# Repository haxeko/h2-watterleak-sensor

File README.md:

# h2-watterleak-sensor

Cảm biến rò rỉ nước chạy pin, kết nối **Matter over Thread**. Chip là **ESP32-H2**, chạy ở chế độ ICD / Sleepy End Device.
Thiết bị dùng được với Apple Home và Home Assistant thông qua Thread Border Router.

## Tiến độ theo giai đoạn

| # | Giai đoạn | Tài liệu | Trạng thái |
|---|---|---|---|
| 1 | Yêu cầu & ngân sách dòng | [docs/01-yeu-cau-va-ngan-sach-dong.md](docs/01-yeu-cau-va-ngan-sach-dong.md) | ✅ Đã chốt |
| 2 | Sơ đồ khối + gán chân GPIO | [docs/02-so-do-khoi-va-gan-chan.md](docs/02-so-do-khoi-va-gan-chan.md) | ✅ Đã chốt |
| 3 | Sơ đồ nguyên lý (KiCad 9) | [docs/03-so-do-nguyen-ly.md](docs/03-so-do-nguyen-ly.md) · [PDF](hardware/h2-leak-sensor/h2-leak-sensor_schematic.pdf) · [project](hardware/) | ✅ Xong, ERC 0 lỗi |
| 4 | Layout PCB, DRC, BOM, CPL, vỏ in 3D | [docs/04-layout-pcb.md](docs/04-layout-pcb.md) · [Gerber zip](hardware/h2-leak-sensor/fab/h2-leak-sensor_gerbers.zip) · [vỏ](hardware/enclosure/) | ✅ Xong, DRC 0 lỗi / 0 cảnh báo, chờ duyệt |
| 5 | Firmware (ESP-IDF v5.5.5 + esp-matter release/v1.6) | [docs/05-firmware.md](docs/05-firmware.md) · [firmware/](firmware/) | ✅ Đã viết code, chờ bạn build thử |
| 6 | Kế hoạch test (dòng ngủ, thử nước, tầm Thread) | [docs/06-ke-hoach-test.md](docs/06-ke-hoach-test.md) | ✅ Kế hoạch + công cụ xong, chờ board |

## Công cụ

| Script | Giai đoạn | Việc |
|---|---|---|
| `tools/power_budget.py` | 1, 6 | Mô hình dòng và tuổi thọ pin |
| `hardware/tools/gen_*.py`, `route.py`, `fab_outputs.py` | 3–4 | Sinh sơ đồ, board, đi dây, file sản xuất (xem [hardware/README.md](hardware/README.md)) |
| `tools/ppk2_analyze.py` | 6 | Phân tích bản ghi PPK2: dòng sàn/TB, poll, độ trễ báo rò, tuổi thọ |
| `tools/leak_test_runner.py` + `tools/leak_sim/` | 6 | Bộ giả lập nước + đo độ trễ / chống báo giả qua Home Assistant |

- `tools/power_budget.py`: mô hình ngân sách dòng và tuổi thọ pin, chỉ dùng thư viện chuẩn Python 3.

  ```sh
  python3 tools/power_budget.py              # in toàn bộ bảng (dùng trong tài liệu GĐ1)
  python3 tools/power_budget.py --sai 10     # thử slow-poll 10 s
  python3 tools/power_budget.py --floor 31.5 # thay sàn ngủ bằng số đo thật (GĐ6)
  ```

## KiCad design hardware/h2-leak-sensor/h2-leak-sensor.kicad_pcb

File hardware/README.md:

# Phần cứng — h2-watterleak-sensor rev A (KiCad 9)

```
hardware/
├── h2-leak-sensor/                 project KiCad 9 (mở h2-leak-sensor.kicad_pro)
│   ├── h2-leak-sensor.kicad_sch    trang gốc (4 sheet con)
│   ├── power.kicad_sch  mcu.kicad_sch  probe.kicad_sch  ui.kicad_sch
│   ├── h2-leak-sensor_schematic.pdf
│   ├── h2-leak-sensor.kicad_pcb    board 70 x 42 mm, 2 lớp, đã đi dây (luật DRC trong .kicad_pro)
│   ├── fab/                        Gerber zip, BOM + CPL cho JLCPCB, PDF lắp ráp, báo cáo DRC
│   ├── bom/h2-leak-sensor_bom.csv  BOM gộp theo giá trị (không gồm module ESP)
│   ├── lib/h2leak.kicad_sym        symbol riêng: ESP32-H2-WROOM-02C, Electrode_Comb
│   ├── lib/h2leak.pretty/          footprint riêng (module, TPS63900 hàn tay, 4020, điện cực)
│   ├── sym-lib-table  fp-lib-table bảng thư viện của project (thư viện "h2leak")
├── enclosure/                      vỏ in 3D: h2-leak-enclosure.scad + 3 file STL
└── tools/
    ├── sexpr.py                    đọc/ghi S-expression của KiCad (không phụ thuộc gì)
    ├── gen_lib.py                  sinh thư viện riêng
    ├── gen_sch.py                  sinh sơ đồ nguyên lý phân cấp
    ├── gen_pcb.py                  đặt linh kiện, luật DRC, vùng đổ GND, keep-out, silkscreen
    ├── route.py                    router A* 2 lớp + đổ GND + sửa liên thông GND
    └── fab_outputs.py              Gerber, drill, BOM/CPL JLCPCB, PDF lắp ráp, DRC
```

## Tái tạo và kiểm tra

Cần KiCad 9 (`kicad-cli`) và Python 3.

```sh
python3 hardware/tools/gen_lib.py
python3 hardware/tools/gen_sch.py
cd hardware/h2-leak-sensor
kicad-cli sch erc --severity-all h2-leak-sensor.kicad_sch          # kỳ vọng: 0 violations
kicad-cli sch export pdf -o h2-leak-sensor_schematic.pdf h2-leak-sensor.kicad_sch
kicad-cli sch export bom --fields 'Reference,Value,Footprint,LCSC,MPN,Manufacturer,${QUANTITY}' \
    --group-by 'Value,Footprint,LCSC' -o bom/h2-leak-sensor_bom.csv h2-leak-sensor.kicad_sch
```

Layout và file sản xuất (cần thêm `numpy`):

```sh
python3 hardware/tools/gen_pcb.py        # đọc netlist từ sơ đồ, đặt linh kiện
python3 hardware/tools/route.py          # đi dây, đổ GND, kiểm tra liên thông GND (~4 phút)
python3 hardware/tools/fab_outputs.py    # fab/: Gerber zip, BOM, CPL, PDF lắp ráp, DRC json
cd hardware/h2-leak-sensor
kicad-cli pcb drc --severity-all --schematic-parity h2-leak-sensor.kicad_pcb   # kỳ vọng: 0 / 0 / 0
```

> `gen_pcb.py` tạo board mới từ đầu, nên mọi chỉnh tay trên board sẽ mất.
> Nếu đã chỉnh tay thì chỉ chạy `route.py --gnd-only` (kiểm tra và sửa liên thông GND) và `fab_outputs.py`.

Tài liệu thiết kế:
- [docs/02-so-do-khoi-va-gan-chan.md](../docs/02-so-do-khoi-va-gan-chan.md): sơ đồ khối và gán chân.
- [docs/03-so-do-nguyen-ly.md](../docs/03-so-do-nguyen-ly.md): sơ đồ nguyên lý.
- [docs/04-layout-pcb.md](../docs/04-layout-pcb.md): layout, DRC, file sản xuất, vỏ.

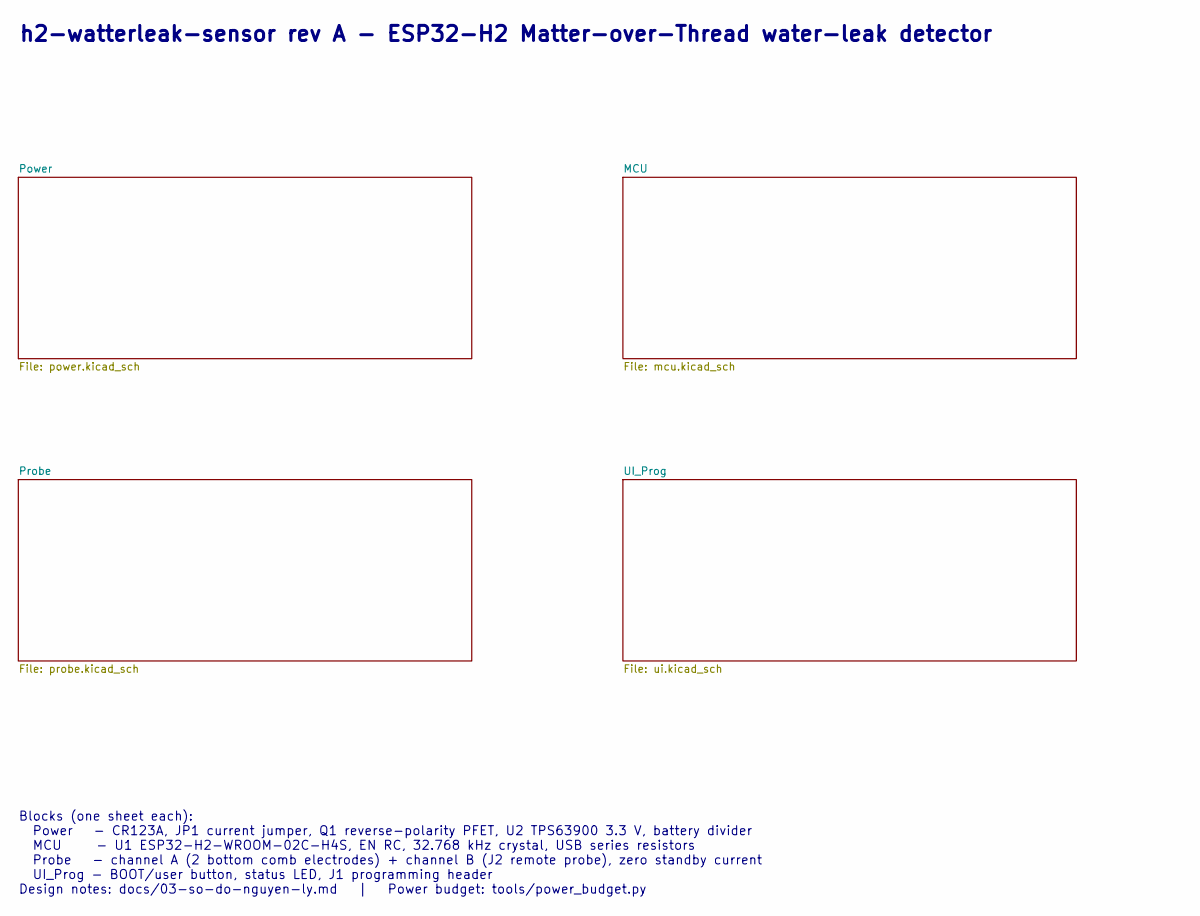
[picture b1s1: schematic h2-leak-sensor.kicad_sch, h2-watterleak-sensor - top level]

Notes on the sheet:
h2-watterleak-sensor rev A - ESP32-H2 Matter-over-Thread water-leak detector
Blocks (one sheet each): Power - CR123A, JP1 current jumper, Q1 reverse-polarity PFET, U2 TPS63900 3.3 V, battery divider MCU - U1 ESP32-H2-WROOM-02C-H4S, EN RC, 32.768 kHz crystal, USB series resistors Probe - channel A (2 bottom comb electrodes) + channel B (J2 remote probe), zero standby current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

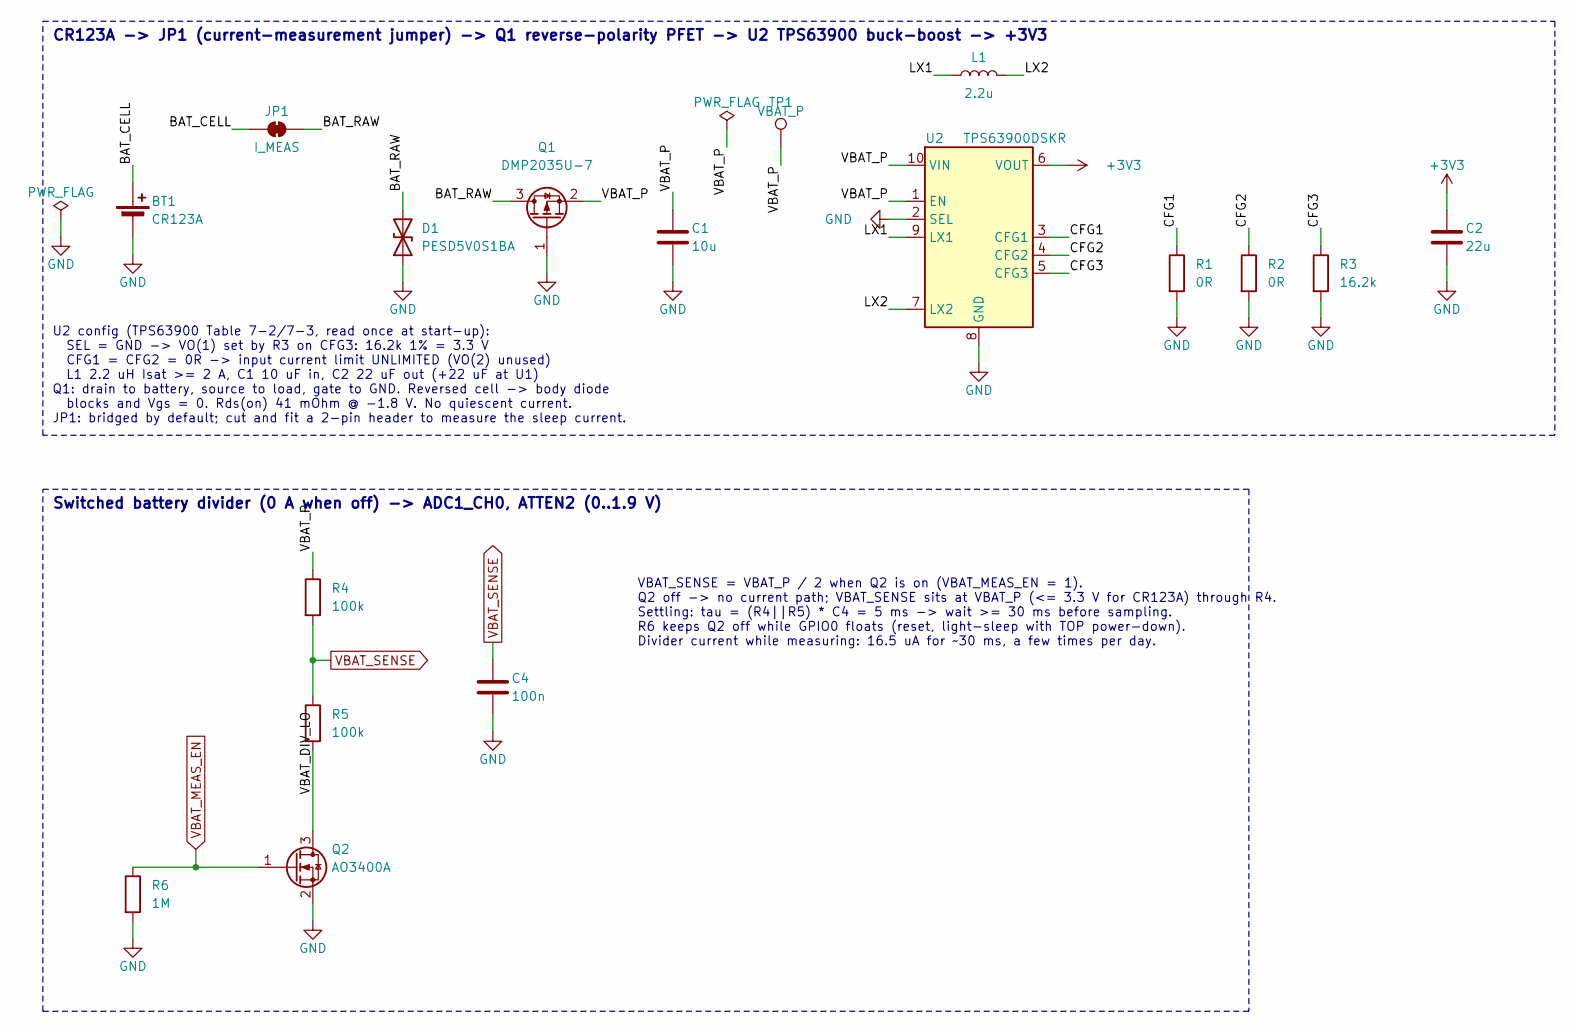
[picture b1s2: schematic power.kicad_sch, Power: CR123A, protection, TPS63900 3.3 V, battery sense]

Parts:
BT1: CR123A; BatteryHolder_Bulgin_BX0123_1xCR123; MPN BX0123 (DigiKey 708-1412-ND)
C1: 10u; C_0603_1608Metric_Pad1.08x0.95mm_HandSolder; MPN CL10A106KP8NNNC; LCSC C19702
C2: 22u; C_0805_2012Metric_Pad1.18x1.45mm_HandSolder; MPN CL21A226MAQNNNE; LCSC C45783
C4: 100n; C_0603_1608Metric_Pad1.08x0.95mm_HandSolder; MPN CC0603KRX7R9BB104; LCSC C14663
D1: PESD5V0S1BA; D_SOD-323_HandSoldering; MPN PESD5V0S1BA,115; LCSC C19224
JP1: I_MEAS; SolderJumper-2_P1.3mm_Bridged_RoundedPad1.0x1.5mm; MPN solder jumper (bridged)
L1: 2.2u; L_Sunlord_WPN4020H_HandSolder; MPN WPN4020H2R2MT; LCSC C98361
Q1: DMP2035U-7; SOT-23_Handsoldering; MPN DMP2035U-7; LCSC C110499
Q2: AO3400A; SOT-23_Handsoldering; MPN AO3400A; LCSC C20917
R1, R2: 0R; R_0603_1608Metric_Pad0.98x0.95mm_HandSolder; MPN 0603WAF0000T5E; LCSC C21189
R3: 16.2k; R_0603_1608Metric_Pad0.98x0.95mm_HandSolder; MPN 0603WAF1622T5E; LCSC C22885
R4, R5: 100k; R_0603_1608Metric_Pad0.98x0.95mm_HandSolder; MPN 0603WAF1003T5E; LCSC C25803
R6: 1M; R_0603_1608Metric_Pad0.98x0.95mm_HandSolder; MPN 0603WAF1004T5E; LCSC C22935
TP1: VBAT_P; TestPoint_Pad_D1.5mm; MPN test pad
U2: TPS63900DSKR; TPS63900_WSON-10_2.5x2.5mm_HandSolder; MPN TPS63900DSKR; LCSC C1518762

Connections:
+3V3: C2.1, U2.6 (VOUT); also elsewhere on the board
/Power/BAT_CELL: BT1.1 (+), JP1.1 (A)
/Power/BAT_RAW: D1.2 (A2), JP1.2 (B), Q1.3 (D)
/Power/CFG1: R1.1, U2.3 (CFG1)
/Power/CFG2: R2.1, U2.4 (CFG2)
/Power/CFG3: R3.1, U2.5 (CFG3)
/Power/LX1: L1.1, U2.9 (LX1)
/Power/LX2: L1.2, U2.7 (LX2)
/Power/VBAT_DIV_LO: Q2.3 (D), R5.2
/Power/VBAT_P: C1.1, Q1.2 (S), R4.1, TP1.1, U2.1 (EN), U2.10 (VIN)
GND: BT1.2 (-), C1.2, C2.2, C4.2, D1.1 (A1), Q1.1 (G), Q2.2 (S), R1.2, R2.2, R3.2, R6.2, U2.2 (SEL), U2.8 (GND), U2.11 (GND); also elsewhere on the board
VBAT_MEAS_EN: Q2.1 (G), R6.1; also elsewhere on the board
VBAT_SENSE: C4.1, R4.2, R5.1; also elsewhere on the board

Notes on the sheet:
CR123A -> JP1 (current-measurement jumper) -> Q1 reverse-polarity PFET -> U2 TPS63900 buck-boost -> +3V3
U2 config (TPS63900 Table 7-2/7-3, read once at start-up): SEL = GND -> VO(1) set by R3 on CFG3: 16.2k 1% = 3.3 V CFG1 = CFG2 = 0R -> input current limit UNLIMITED (VO(2) unused) L1 2.2 uH Isat >= 2 A, C1 10 uF in, C2 22 uF out (+22 uF at U1) Q1: drain to battery, source to load, gate to GND. Rever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
Switched battery divider (0 A when off) -> ADC1_CH0, ATTEN2 (0..1.9 V)
VBAT_SENSE = VBAT_P / 2 when Q2 is on (VBAT_MEAS_EN = 1). Q2 off -> no current path; VBAT_SENSE sits at VBAT_P (<= 3.3 V for CR123A) through R4. Settling: tau = (R4||R5) * C4 = 5 ms -> wait >= 30 ms before sampling. R6 keeps Q2 off while GPIO0 floats (reset, light-sleep with TOP power-down). Divide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

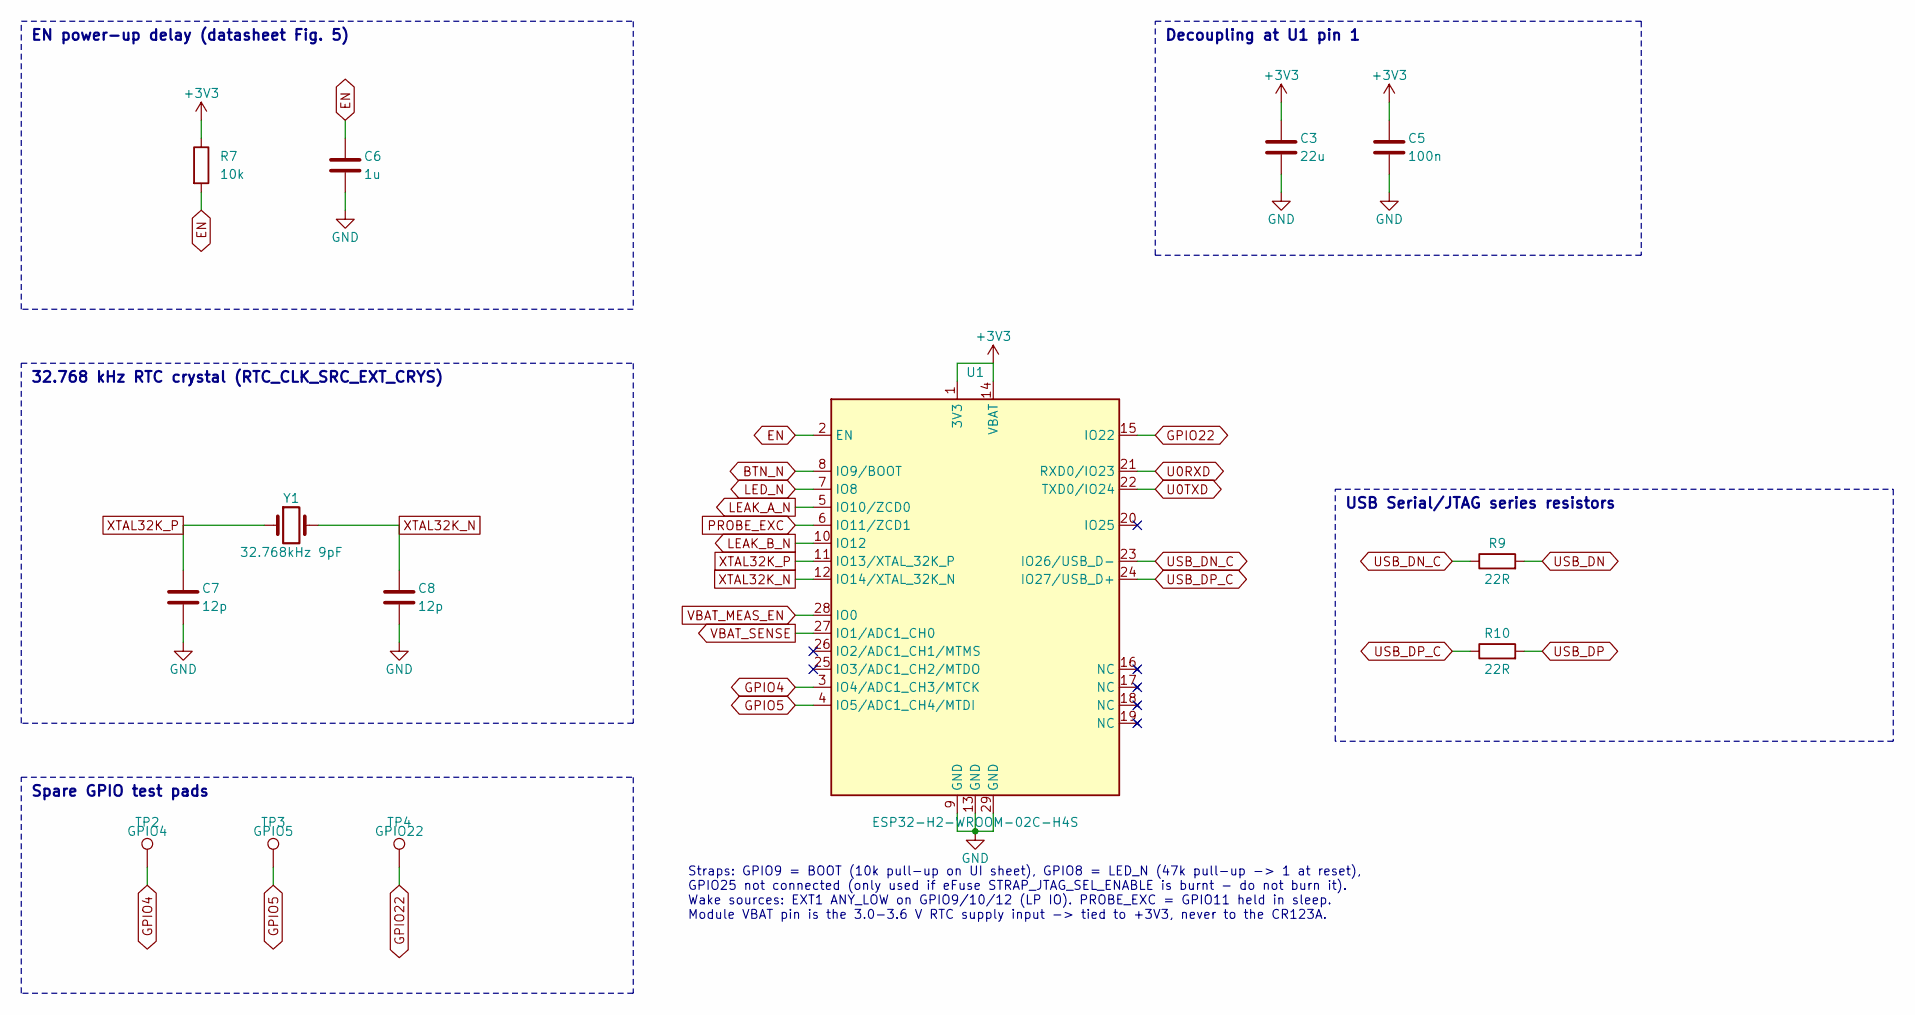
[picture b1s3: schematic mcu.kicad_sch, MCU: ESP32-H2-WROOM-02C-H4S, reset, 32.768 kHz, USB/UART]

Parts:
C3: 22u; C_0805_2012Metric_Pad1.18x1.45mm_HandSolder; MPN CL21A226MAQNNNE; LCSC C45783
C5: 100n; C_0603_1608Metric_Pad1.08x0.95mm_HandSolder; MPN CC0603KRX7R9BB104; LCSC C14663
C6: 1u; C_0603_1608Metric_Pad1.08x0.95mm_HandSolder; MPN CL10A105KB8NNNC; LCSC C15849
C7, C8: 12p; C_0603_1608Metric_Pad1.08x0.95mm_HandSolder; MPN CL10C120JB8NNNC; LCSC C38523
R7: 10k; R_0603_1608Metric_Pad0.98x0.95mm_HandSolder; MPN 0603WAF1002T5E; LCSC C25804
R9, R10: 22R; R_0603_1608Metric_Pad0.98x0.95mm_HandSolder; MPN 0603WAF220JT5E; LCSC C23345
TP2: GPIO4; TestPoint_Pad_D1.5mm; MPN test pad
TP3: GPIO5; TestPoint_Pad_D1.5mm; MPN test pad
TP4: GPIO22; TestPoint_Pad_D1.5mm; MPN test pad
U1: ESP32-H2-WROOM-02C-H4S; ESP32-H2-WROOM-02C; MPN ESP32-H2-WROOM-02C-H4S
Y1: 32.768kHz 9pF; Crystal_SMD_3215-2Pin_3.2x1.5mm; MPN Q13FC13500003; LCSC C99010

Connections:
+3V3: C3.1, C5.1, R7.1, U1.1 (3V3), U1.14 (VBAT); also elsewhere on the board
BTN_N: U1.8 (IO9/BOOT); also elsewhere on the board
EN: C6.1, R7.2, U1.2 (EN); also elsewhere on the board
GND: C3.2, C5.2, C6.2, C7.2, C8.2, U1.9 (GND), U1.13 (GND), U1.29 (GND); also elsewhere on the board
GPIO4: TP2.1, U1.3 (IO4/ADC1_CH3/MTCK)
GPIO5: TP3.1, U1.4 (IO5/ADC1_CH4/MTDI)
GPIO22: TP4.1, U1.15 (IO22)
LEAK_A_N: U1.5 (IO10/ZCD0); also elsewhere on the board
LEAK_B_N: U1.10 (IO12); also elsewhere on the board
LED_N: U1.7 (IO8); also elsewhere on the board
PROBE_EXC: U1.6 (IO11/ZCD1); also elsewhere on the board
U0RXD: U1.21 (RXD0/IO23); also elsewhere on the board
U0TXD: U1.22 (TXD0/IO24); also elsewhere on the board
USB_DN: R9.2; also elsewhere on the board
USB_DN_C: R9.1, U1.23 (IO26/USB_D-)
USB_DP: R10.2; also elsewhere on the board
USB_DP_C: R10.1, U1.24 (IO27/USB_D+)
VBAT_MEAS_EN: U1.28 (IO0); also elsewhere on the board
VBAT_SENSE: U1.27 (IO1/ADC1_CH0); also elsewhere on the board
XTAL32K_N: C8.1, U1.12 (IO14/XTAL_32K_N), Y1.2
XTAL32K_P: C7.1, U1.11 (IO13/XTAL_32K_P), Y1.1

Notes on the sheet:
Decoupling at U1 pin 1
EN power-up delay (datasheet Fig. 5)
32.768 kHz RTC crystal (RTC_CLK_SRC_EXT_CRYS)
USB Serial/JTAG series resistors
Spare GPIO test pads
Straps: GPIO9 = BOOT (10k pull-up on UI sheet), GPIO8 = LED_N (47k pull-up -> 1 at reset), GPIO25 not connected (only used if eFuse STRAP_JTAG_SEL_ENABLE is burnt - do not burn it). Wake sources: EXT1 ANY_LOW on GPIO9/10/12 (LP IO). PROBE_EXC = GPIO11 held in sleep. Module VBAT pin is the 3.0-3.6 V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

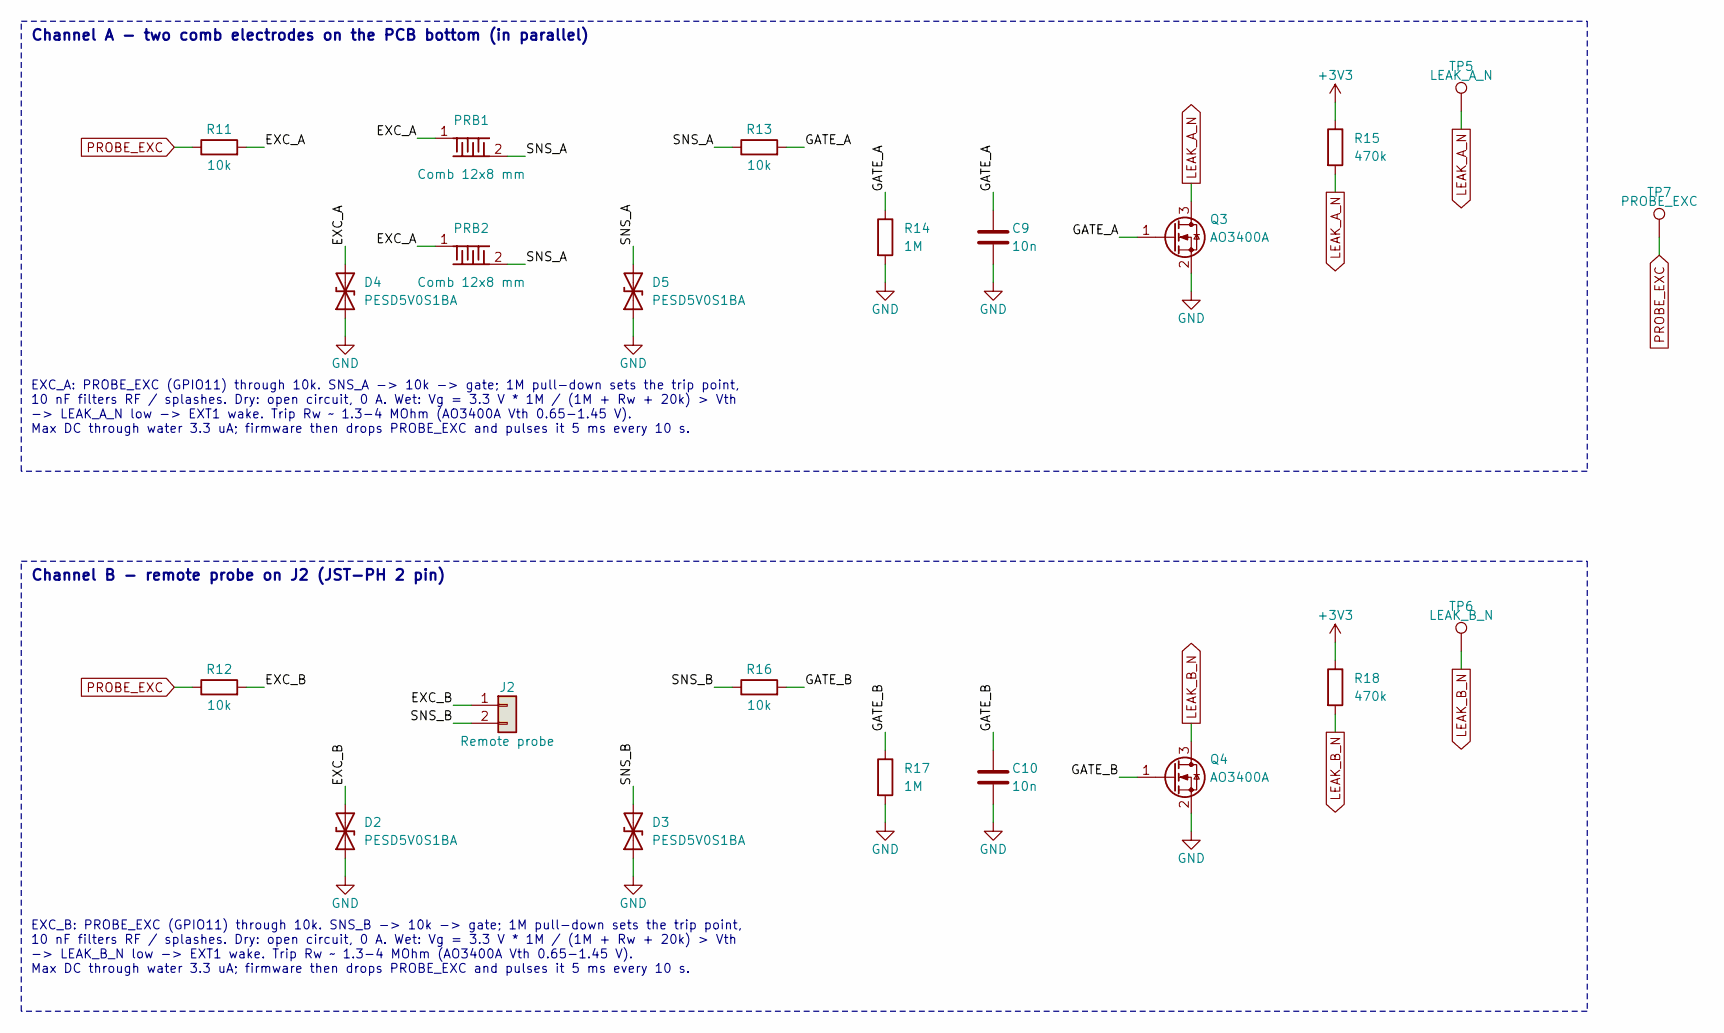
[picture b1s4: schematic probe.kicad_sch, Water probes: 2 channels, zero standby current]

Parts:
C9, C10: 10n; C_0603_1608Metric_Pad1.08x0.95mm_HandSolder; MPN 0603B103K500NT; LCSC C57112
D2, D3, D4, D5: PESD5V0S1BA; D_SOD-323_HandSoldering; MPN PESD5V0S1BA,115; LCSC C19224
J2: Remote probe; JST_PH_S2B-PH-K_1x02_P2.00mm_Horizontal; MPN S2B-PH-K-S(LF)(SN); LCSC C173752
PRB1, PRB2: Comb 12x8 mm; Electrode_Comb_12x8mm; MPN PCB copper (ENIG)
Q3, Q4: AO3400A; SOT-23_Handsoldering; MPN AO3400A; LCSC C20917
R11, R12, R13, R16: 10k; R_0603_1608Metric_Pad0.98x0.95mm_HandSolder; MPN 0603WAF1002T5E; LCSC C25804
R14, R17: 1M; R_0603_1608Metric_Pad0.98x0.95mm_HandSolder; MPN 0603WAF1004T5E; LCSC C22935
R15, R18: 470k; R_0603_1608Metric_Pad0.98x0.95mm_HandSolder; MPN 0603WAF4703T5E; LCSC C23178
TP5: LEAK_A_N; TestPoint_Pad_D1.5mm; MPN test pad
TP6: LEAK_B_N; TestPoint_Pad_D1.5mm; MPN test pad
TP7: PROBE_EXC; TestPoint_Pad_D1.5mm; MPN test pad

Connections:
+3V3: R15.1, R18.1; also elsewhere on the board
/Probe/EXC_A: D4.2 (A2), PRB1.1 (EXC), PRB2.1 (EXC), R11.2
/Probe/EXC_B: D2.2 (A2), J2.1, R12.2
/Probe/GATE_A: C9.1, Q3.1 (G), R13.2, R14.1
/Probe/GATE_B: C10.1, Q4.1 (G), R16.2, R17.1
/Probe/SNS_A: D5.2 (A2), PRB1.2 (SNS), PRB2.2 (SNS), R13.1
/Probe/SNS_B: D3.2 (A2), J2.2, R16.1
GND: C9.2, C10.2, D2.1 (A1), D3.1 (A1), D4.1 (A1), D5.1 (A1), Q3.2 (S), Q4.2 (S), R14.2, R17.2; also elsewhere on the board
LEAK_A_N: Q3.3 (D), R15.2, TP5.1; also elsewhere on the board
LEAK_B_N: Q4.3 (D), R18.2, TP6.1; also elsewhere on the board
PROBE_EXC: R11.1, R12.1, TP7.1; also elsewhere on the board

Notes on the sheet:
Channel A - two comb electrodes on the PCB bottom (in parallel)
EXC_A: PROBE_EXC (GPIO11) through 10k. SNS_A -> 10k -> gate; 1M pull-down sets the trip point, 10 nF filters RF / splashes. Dry: open circuit, 0 A. Wet: Vg = 3.3 V * 1M / (1M + Rw + 20k) > Vth -> LEAK_A_N low -> EXT1 wake. Trip Rw ~ 1.3-4 MOhm (AO3400A Vth 0.65-1.45 V). Max DC through water 3.3 uA;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
Channel B - remote probe on J2 (JST-PH 2 pin)
EXC_B: PROBE_EXC (GPIO11) through 10k. SNS_B -> 10k -> gate; 1M pull-down sets the trip point, 10 nF filters RF / splashes. Dry: open circuit, 0 A. Wet: Vg = 3.3 V * 1M / (1M + Rw + 20k) > Vth -> LEAK_B_N low -> EXT1 wake. Trip Rw ~ 1.3-4 MOhm (AO3400A Vth 0.65-1.45 V). Max DC through water 3.3 uA;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

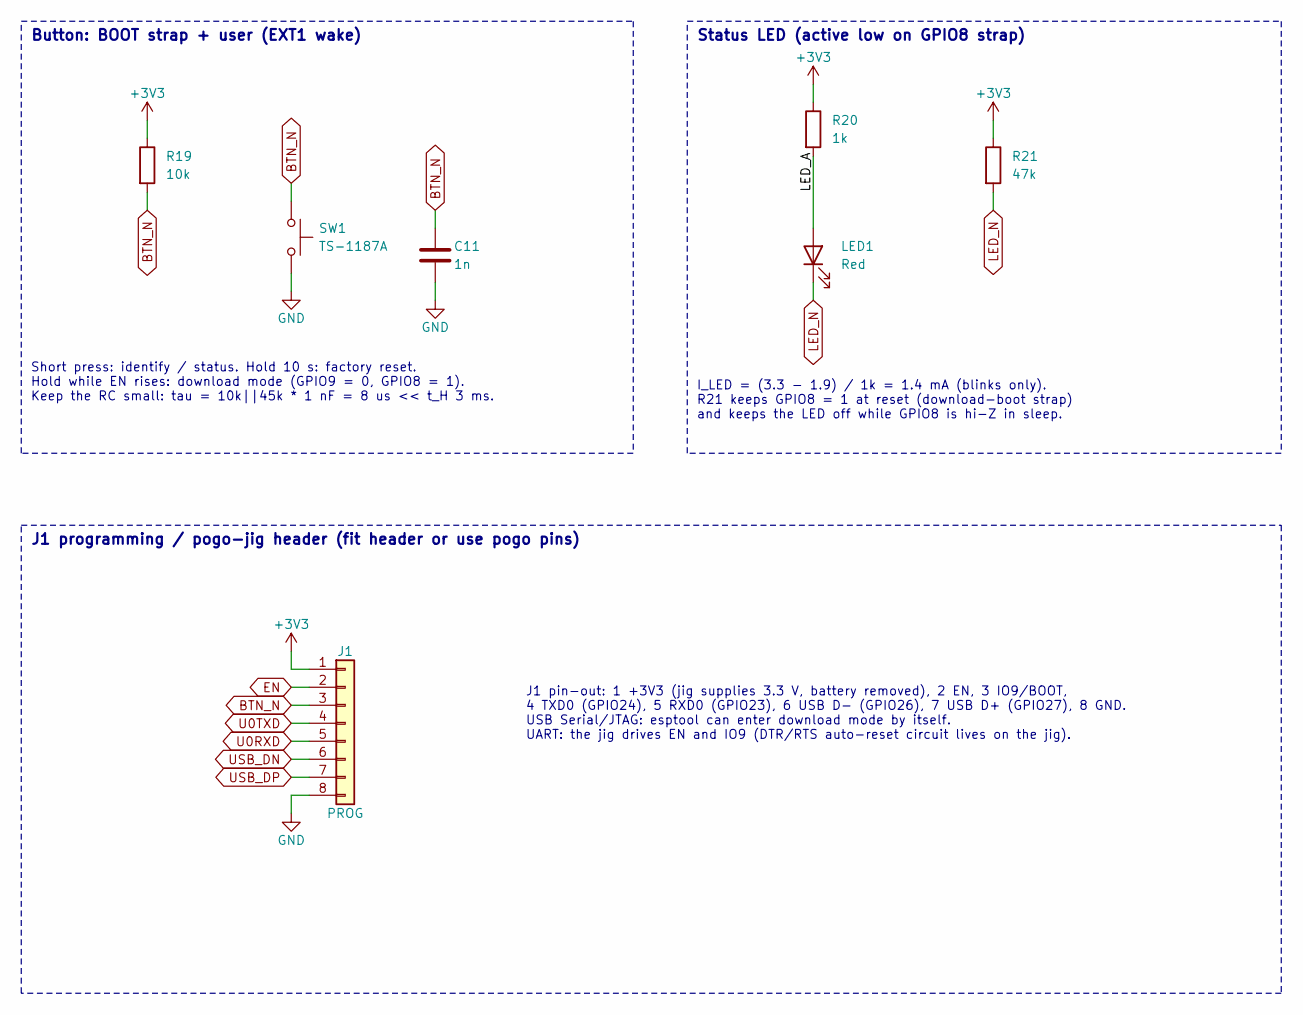
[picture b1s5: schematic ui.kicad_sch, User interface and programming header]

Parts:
C11: 1n; C_0603_1608Metric_Pad1.08x0.95mm_HandSolder; MPN CL10B102KB8NNNC; LCSC C1588
J1: PROG; PinHeader_1x08_P2.54mm_Vertical; MPN 2.54 mm 1x08 header / pogo pads
LED1: Red; LED_0603_1608Metric_Pad1.05x0.95mm_HandSolder; MPN KT-0603R; LCSC C2286
R19: 10k; R_0603_1608Metric_Pad0.98x0.95mm_HandSolder; MPN 0603WAF1002T5E; LCSC C25804
R20: 1k; R_0603_1608Metric_Pad0.98x0.95mm_HandSolder; MPN 0603WAF1001T5E; LCSC C21190
R21: 47k; R_0603_1608Metric_Pad0.98x0.95mm_HandSolder; MPN 0603WAF4702T5E; LCSC C25819
SW1: TS-1187A; SW_Push_1P1T_XKB_TS-1187A; MPN TS-1187A-B-A-B; LCSC C318884

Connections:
+3V3: J1.1, R19.1, R20.1, R21.1; also elsewhere on the board
/UI_Prog/LED_A: LED1.2 (A), R20.2
BTN_N: C11.1, J1.3, R19.2, SW1.1; also elsewhere on the board
EN: J1.2; also elsewhere on the board
GND: C11.2, J1.8, SW1.2; also elsewhere on the board
LED_N: LED1.1 (K), R21.2; also elsewhere on the board
U0RXD: J1.5; also elsewhere on the board
U0TXD: J1.4; also elsewhere on the board
USB_DN: J1.6; also elsewhere on the board
USB_DP: J1.7; also elsewhere on the board

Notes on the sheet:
Button: BOOT strap + user (EXT1 wake)
Short press: identify / status. Hold 10 s: factory reset. Hold while EN rises: download mode (GPIO9 = 0, GPIO8 = 1). Keep the RC small: tau = 10k||45k * 1 nF = 8 us << t_H 3 ms.
Status LED (active low on GPIO8 strap)
I_LED = (3.3 - 1.9) / 1k = 1.4 mA (blinks only). R21 keeps GPIO8 = 1 at reset (download-boot strap) and keeps the LED off while GPIO8 is hi-Z in sleep.
J1 programming / pogo-jig header (fit header or use pogo pins)
J1 pin-out: 1 +3V3 (jig supplies 3.3 V, battery removed), 2 EN, 3 IO9/BOOT, 4 TXD0 (GPIO24), 5 RXD0 (GPIO23), 6 USB D- (GPIO26), 7 USB D+ (GPIO27), 8 GND. USB Serial/JTAG: esptool can enter download mode by itself. UART: the jig drives EN and IO9 (DTR/RTS auto-reset circuit lives on the jig).

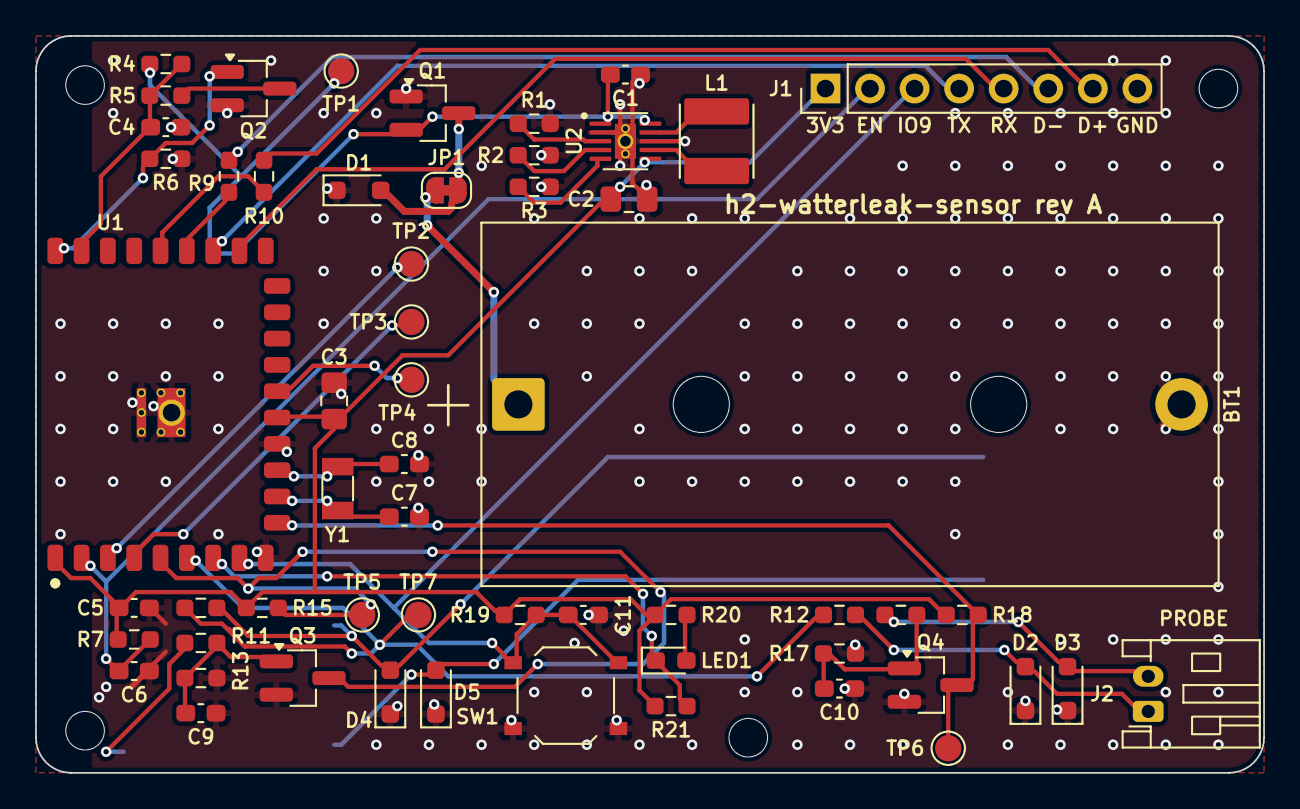
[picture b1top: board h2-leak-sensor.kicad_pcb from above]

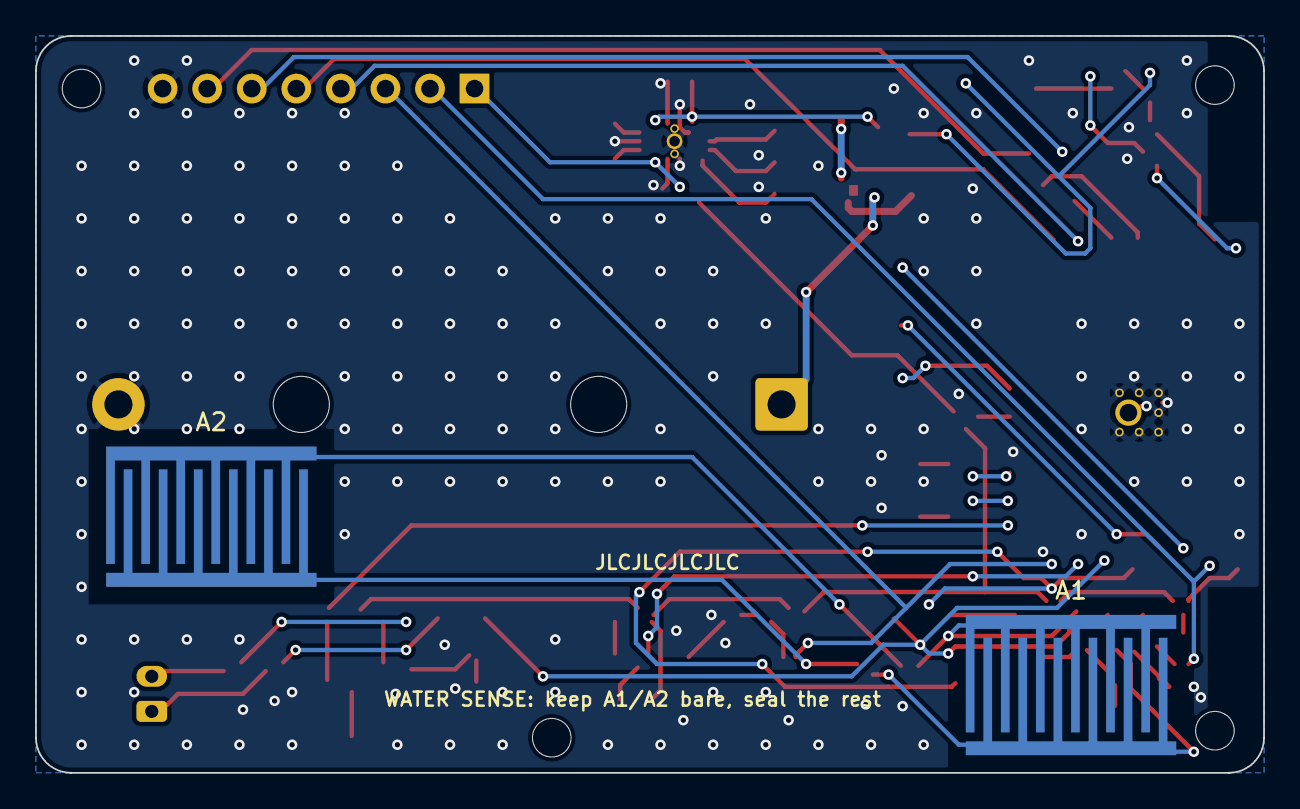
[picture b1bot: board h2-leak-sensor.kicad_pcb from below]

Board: 2 copper layers, 70.0 x 42.0 mm, 63 parts (2 on the bottom side), 37 nets.

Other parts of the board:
H1, H2, H3, H4: MountingHole_M2; MountingHole_2.2mm_M2

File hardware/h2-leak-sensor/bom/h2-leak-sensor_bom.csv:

"Refs","Value","Footprint","LCSC","MPN","Manufacturer","Qty"
"BT1","CR123A","Battery:BatteryHolder_Bulgin_BX0123_1xCR123","","BX0123 (DigiKey 708-1412-ND)","Bulgin","1"
"C1","10u","Capacitor_SMD:C_0603_1608Metric_Pad1.08x0.95mm_HandSolder","C19702","CL10A106KP8NNNC","Samsung","1"
"C2,C3","22u","Capacitor_SMD:C_0805_2012Metric_Pad1.18x1.45mm_HandSolder","C45783","CL21A226MAQNNNE","Samsung","2"
"C4,C5","100n","Capacitor_SMD:C_0603_1608Metric_Pad1.08x0.95mm_HandSolder","C14663","CC0603KRX7R9BB104","YAGEO","2"
"C6","1u","Capacitor_SMD:C_0603_1608Metric_Pad1.08x0.95mm_HandSolder","C15849","CL10A105KB8NNNC","Samsung","1"
"C7,C8","12p","Capacitor_SMD:C_0603_1608Metric_Pad1.08x0.95mm_HandSolder","C38523","CL10C120JB8NNNC","Samsung","2"
"C9,C10","10n","Capacitor_SMD:C_0603_1608Metric_Pad1.08x0.95mm_HandSolder","C57112","0603B103K500NT","FH","2"
"C11","1n","Capacitor_SMD:C_0603_1608Metric_Pad1.08x0.95mm_HandSolder","C1588","CL10B102KB8NNNC","Samsung","1"
"D1-D5","PESD5V0S1BA","Diode_SMD:D_SOD-323_HandSoldering","C19224","PESD5V0S1BA,115","Nexperia","5"
"J1","PROG","Connector_PinHeader_2.54mm:PinHeader_1x08_P2.54mm_Vertical","","2.54 mm 1x08 header / pogo pads","-","1"
"J2","Remote probe","Connector_JST:JST_PH_S2B-PH-K_1x02_P2.00mm_Horizontal","C173752","S2B-PH-K-S(LF)(SN)","JST","1"
"L1","2.2u","h2leak:L_Sunlord_WPN4020H_HandSolder","C98361","WPN4020H2R2MT","Sunlord","1"
"LED1","Red","LED_SMD:LED_0603_1608Metric_Pad1.05x0.95mm_HandSolder","C2286","KT-0603R","Hubei KENTO","1"
"Q1","DMP2035U-7","Package_TO_SOT_SMD:SOT-23_Handsoldering","C110499","DMP2035U-7","Diodes Inc","1"
"Q2-Q4","AO3400A","Package_TO_SOT_SMD:SOT-23_Handsoldering","C20917","AO3400A","AOS","3"
"R1,R2","0R","Resistor_SMD:R_0603_1608Metric_Pad0.98x0.95mm_HandSolder","C21189","0603WAF0000T5E","UNI-ROYAL","2"
"R3","16.2k","Resistor_SMD:R_0603_1608Metric_Pad0.98x0.95mm_HandSolder","C22885","0603WAF1622T5E","UNI-ROYAL","1"
"R4,R5","100k","Resistor_SMD:R_0603_1608Metric_Pad0.98x0.95mm_HandSolder","C25803","0603WAF1003T5E","UNI-ROYAL","2"
"R6,R14,R17","1M","Resistor_SMD:R_0603_1608Metric_Pad0.98x0.95mm_HandSolder","C22935","0603WAF1004T5E","UNI-ROYAL","3"
"R7,R11-R13,R16,R19","10k","Resistor_SMD:R_0603_1608Metric_Pad0.98x0.95mm_HandSolder","C25804","0603WAF1002T5E","UNI-ROYAL","6"
"R9,R10","22R","Resistor_SMD:R_0603_1608Metric_Pad0.98x0.95mm_HandSolder","C23345","0603WAF220JT5E","UNI-ROYAL","2"
"R15,R18","470k","Resistor_SMD:R_0603_1608Metric_Pad0.98x0.95mm_HandSolder","C23178","0603WAF4703T5E","UNI-ROYAL","2"
"R20","1k","Resistor_SMD:R_0603_1608Metric_Pad0.98x0.95mm_HandSolder","C21190","0603WAF1001T5E","UNI-ROYAL","1"
"R21","47k","Resistor_SMD:R_0603_1608Metric_Pad0.98x0.95mm_HandSolder","C25819","0603WAF4702T5E","UNI-ROYAL","1"
"SW1","TS-1187A","Button_Switch_SMD:SW_Push_1P1T_XKB_TS-1187A","C318884","TS-1187A-B-A-B","XKB","1"
"U2","TPS63900DSKR","h2leak:TPS63900_WSON-10_2.5x2.5mm_HandSolder","C1518762","TPS63900DSKR","Texas Instruments","1"
"Y1","32.768kHz 9pF","Crystal:Crystal_SMD_3215-2Pin_3.2x1.5mm","C99010","Q13FC13500003","Seiko Epson","1"

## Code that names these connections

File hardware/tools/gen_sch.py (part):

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    "VBAT_SENSE": "output", "VBAT_MEAS_EN": "input",
    "U0TXD": "bidirectional", "U0RXD": "bidirectional", "USB_DN": "bidirectional", "USB_DP": "bidirectional",
    "XTAL32K_P": "passive", "XTAL32K_N": "passive", "USB_DN_C": "bidirectional", "USB_DP_C": "bidirectional",
    "GPIO4": "bidirectional", "GPIO5": "bidirectional", "GPIO22": "bidirectional",
}


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    sh.connect(u1, {
        "2": "EN", "8": "BTN_N", "7": "LED_N", "5": "LEAK_A_N", "6": "PROBE_EXC", "10": "LEAK_B_N",
        "11": "XTAL32K_P", "12": "XTAL32K_N", "28": "VBAT_MEAS_EN", "27": "VBAT_SENSE",
        "26": None, "25": None, "3": "GPIO4", "4": "GPIO5",
        "15": "GPIO22", "21": "U0RXD", "22": "U0TXD", "20": None, "23": "USB_DN_C", "24": "USB_DP_C",
        "16": None, "17": None, "18": None, "19": None})
    sh.box(172.72, 22.86, 241.3, 55.88, "Decoupling at U1 pin 1")
    C(sh, "C3", "22u", "C_22u", 190.5, 40.64, 0, "+3V3", "GND", fp="C0805")
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    R(sh, "R9", "22R", "R_22", 220.98, 99.06, 90, "USB_DN_C", "USB_DN")
    R(sh, "R10", "22R", "R_22", 220.98, 111.76, 90, "USB_DP_C", "USB_DP")
    sh.box(12.7, 129.54, 99.06, 160.02, "Spare GPIO test pads")
    TP(sh, "TP2", 30.48, 142.24, "GPIO4")
    TP(sh, "TP3", 48.26, 142.24, "GPIO5")
    TP(sh, "TP4", 66.04, 142.24, "GPIO22")
    sh.note("Straps: GPIO9 = BOOT (10k pull-up on UI sheet), GPIO8 = LED_N (47k pull-up -> 1 at reset),\n"
            "GPIO25 not connected (only used if eFuse STRAP_JTAG_SEL_ENABLE is burnt - do not burn it).\n"
            "Wake sources: EXT1 ANY_LOW on GPIO9/10/12 (LP IO). PROBE_EXC = GPIO11 held in sleep.\n"
            "Module VBAT pin is the 3.0-3.6 V RTC supply input -> tied to +3V3, never to the CR123A.",
            106.68, 142.24, 1.27)
    return sh
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        NMOS(sh, rs[5], 175.26, y0 + 20.32, gate, leak)
        R(sh, rs[3], "470k", "R_470k", 198.12, y0 + 7.62, 0, "+3V3", leak)
        TP(sh, "TP5" if ch == "A" else "TP6", 215.9, y0 + 2.54, leak)
        sh.note(f"{exc}: PROBE_EXC (GPIO11) through 10k. {sns} -> 10k -> gate; 1M pull-down sets the trip point,\n"
                "10 nF filters RF / splashes. Dry: open circuit, 0 A. Wet: Vg = 3.3 V * 1M / (1M + Rw + 20k) > Vth\n"
                f"-> {leak} low -> EXT1 wake. Trip Rw ~ 1.3-4 MOhm (AO3400A Vth 0.65-1.45 V).\n"
                "Max DC through water 3.3 uA; firmware then drops PROBE_EXC and pulses it 5 ms every 10 s.",
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
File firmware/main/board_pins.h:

/*
 * h2-watterleak-sensor rev A - ESP32-H2-WROOM-02C-H4S pin map
 * Source of truth: docs/02-so-do-khoi-va-gan-chan.md (sections 3, 5, 7) and the KiCad schematic.
 */
#pragma once

#include "driver/gpio.h"
#include "hal/adc_types.h"
#include "esp_bit_defs.h"

#define PIN_VBAT_MEAS_EN   GPIO_NUM_0   /* out, active-high, ext. 1 MOhm pull-down on the Q2 gate       */
#define PIN_VBAT_SENSE     GPIO_NUM_1   /* ADC1_CH0, divider 100k/100k (x2), 100 nF                      */
#define PIN_LED_N          GPIO_NUM_8   /* LP IO, out, active-low, ext. 47 kOhm pull-up (strap pin)       */
#define PIN_BUTTON_N       GPIO_NUM_9   /* LP IO, in, active-low, ext. 10 kOhm pull-up (BOOT strap)       */
#define PIN_LEAK_A_N       GPIO_NUM_10  /* LP IO, in, active-low, ext. 470 kOhm pull-up - bottom combs A1/A2 */
#define PIN_PROBE_EXC      GPIO_NUM_11  /* LP IO, out, 1 = both probes biased ("armed"), held in sleep    */
#define PIN_LEAK_B_N       GPIO_NUM_12  /* LP IO, in, active-low, ext. 470 kOhm pull-up - remote probe J2 */
/* GPIO13/14: 32.768 kHz crystal Y1 (CONFIG_RTC_CLK_SRC_EXT_CRYS=y)                                         */
/* GPIO23/24: UART0 console on J1, GPIO26/27: USB D-/D+ on J1                                                 */

/* Not connected or test pads only: parked as inputs with pull-down (HW guideline: no floating inputs). */
#define UNUSED_PIN_MASK    (BIT64(GPIO_NUM_2) | BIT64(GPIO_NUM_3) | BIT64(GPIO_NUM_4) | BIT64(GPIO_NUM_5) | \
                            BIT64(GPIO_NUM_22) | BIT64(GPIO_NUM_25))

#define VBAT_ADC_UNIT      ADC_UNIT_1
#define VBAT_ADC_CHANNEL   ADC_CHANNEL_0
#define VBAT_ADC_ATTEN     ADC_ATTEN_DB_6      /* ATTEN2 on ESP32-H2: 0 .. about 1.9 V                  */
#define VBAT_DIVIDER_NUM   2
#define VBAT_SETTLE_MS     30                  /* about 6 tau, tau = (100k || 100k) * 100 nF = 5 ms     */

/* Wake-up inputs: all active-low LP IOs -> EXT1 "any low" (works with the TOP domain powered down). */
#define WAKE_MASK_BUTTON   BIT64(PIN_BUTTON_N)
#define WAKE_MASK_LEAK     (BIT64(PIN_LEAK_A_N) | BIT64(PIN_LEAK_B_N))
#define WAKE_EXT1_MASK     (WAKE_MASK_BUTTON | WAKE_MASK_LEAK)
